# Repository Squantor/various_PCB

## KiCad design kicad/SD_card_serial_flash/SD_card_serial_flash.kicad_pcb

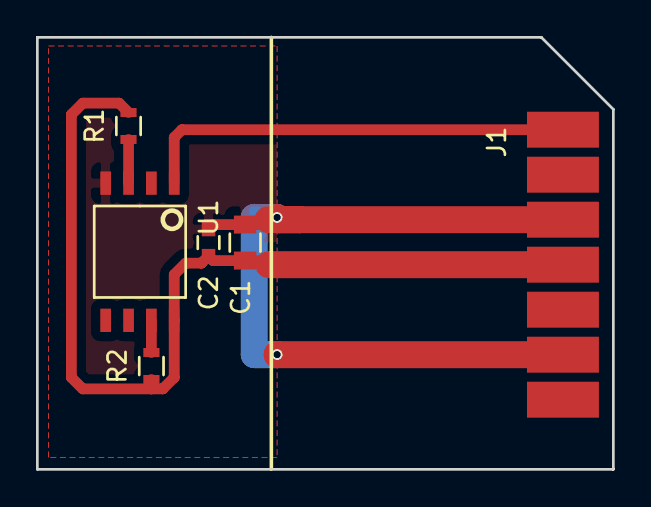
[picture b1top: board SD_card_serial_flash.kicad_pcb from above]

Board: 2 copper layers, 32.0 x 24.0 mm, 6 parts (0 on the bottom side), 8 nets.

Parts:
C1: 1u; C_0805
C2: 100n; C_0603
J1: SD_CARD_connector
R1: 10K; R_0603
R2: 10k; R_0603
U1: W25Q32BV; W25Q32BVST

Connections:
+3V3: C1.1, C2.1, J1.4, R1.2, R2.1, U1.8
CS: J1.1, U1.1
DI: J1.2, U1.5
DO: J1.7, U1.2
GND: C1.2, C2.2, J1.3, J1.6, U1.4
unnamed: R1.1, U1.3
unnamed: R2.2, U1.7
SCLK: J1.5, U1.6

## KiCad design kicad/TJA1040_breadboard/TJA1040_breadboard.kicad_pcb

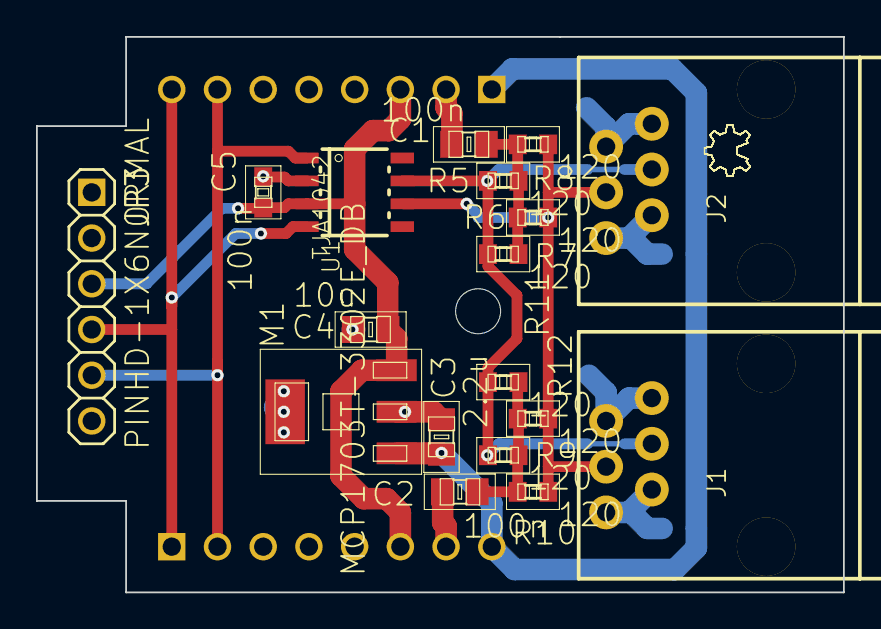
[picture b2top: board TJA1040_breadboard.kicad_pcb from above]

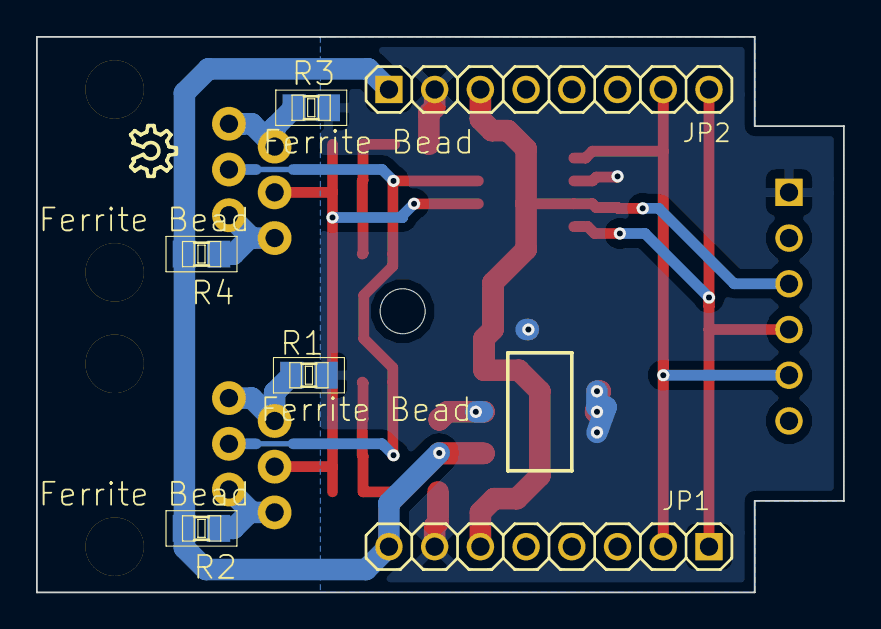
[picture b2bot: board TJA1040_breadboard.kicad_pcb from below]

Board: 2 copper layers, 44.8 x 30.9 mm, 25 parts (5 on the bottom side), 13 nets.

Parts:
C1, C2: 100n; SquantorRCL-C0805
C3: 2.2u; SquantorRCL-C0805
C4: 10u; SquantorRCL-C0805
C5: 100n; SquantorRCL-C0603
J1, J2: SquantBus_RJ11; SquantBus-RJ11
JP1, JP2: PINHD-1X8TH_NORMAL; SquantorConnectors-1X08
JP3: PINHD-1X6NORMAL; SquantorConnectors-1X06
LOGO1: OSHW_LOGO_8MILX0100-NT; ohw-logo-OSHW_8X100_NOTEXT
M1: MCP1703T-3302E_DB; SquantorMicrochip-SOT223
R1, R2, R3, R4: Ferrite Bead; SquantorRCL-R0805
R5, R6, R7, R8, R9, R10, R11, R12: 120; SquantorRCL-R0603
U1: TJA1042; SOT96-1

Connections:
+5V: C4.1, C5.2, JP1.6, JP2.3, JP3.3, M1.3, U1.3
+BATT: C3.1, JP1.8, JP2.1, M1.1, R2.2, R4.2
CAN_H: J1.4, J2.4, R5.1, R7.1, R9.1, R11.1, U1.7
CAN_L: J1.3, J2.3, R6.2, R8.2, R10.2, R12.2, U1.6
CAN_RX: JP1.1, JP2.8, JP3.4, U1.4
CAN_TX: JP1.2, JP2.7, JP3.5, U1.1
GND: C1.2, C2.1, C3.2, C4.2, C5.1, JP1.7, JP2.2, JP3.1, M1.2, M1.4, R1.2, R3.2, U1.2
unnamed: C1.1, R5.2, R6.1, R7.2, R8.1
unnamed: C2.2, R9.2, R10.1, R11.2, R12.1
unnamed: J1.1, J1.2, R2.1
unnamed: J1.5, J1.6, R1.1
unnamed: J2.1, J2.2, R4.1
unnamed: J2.5, J2.6, R3.1

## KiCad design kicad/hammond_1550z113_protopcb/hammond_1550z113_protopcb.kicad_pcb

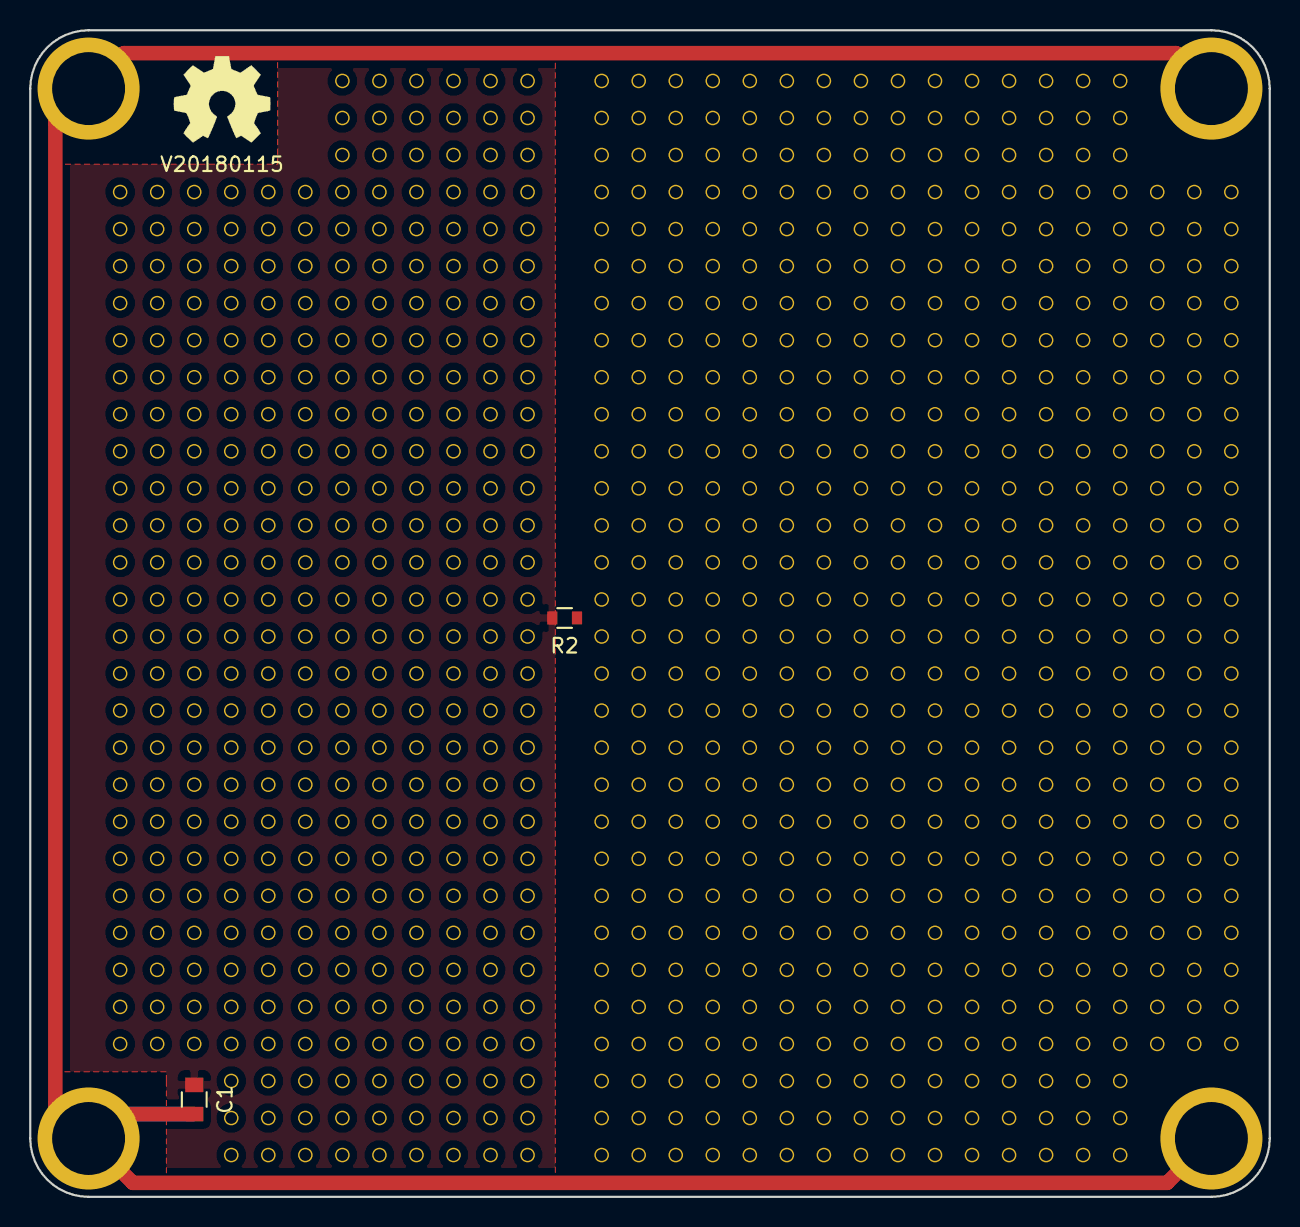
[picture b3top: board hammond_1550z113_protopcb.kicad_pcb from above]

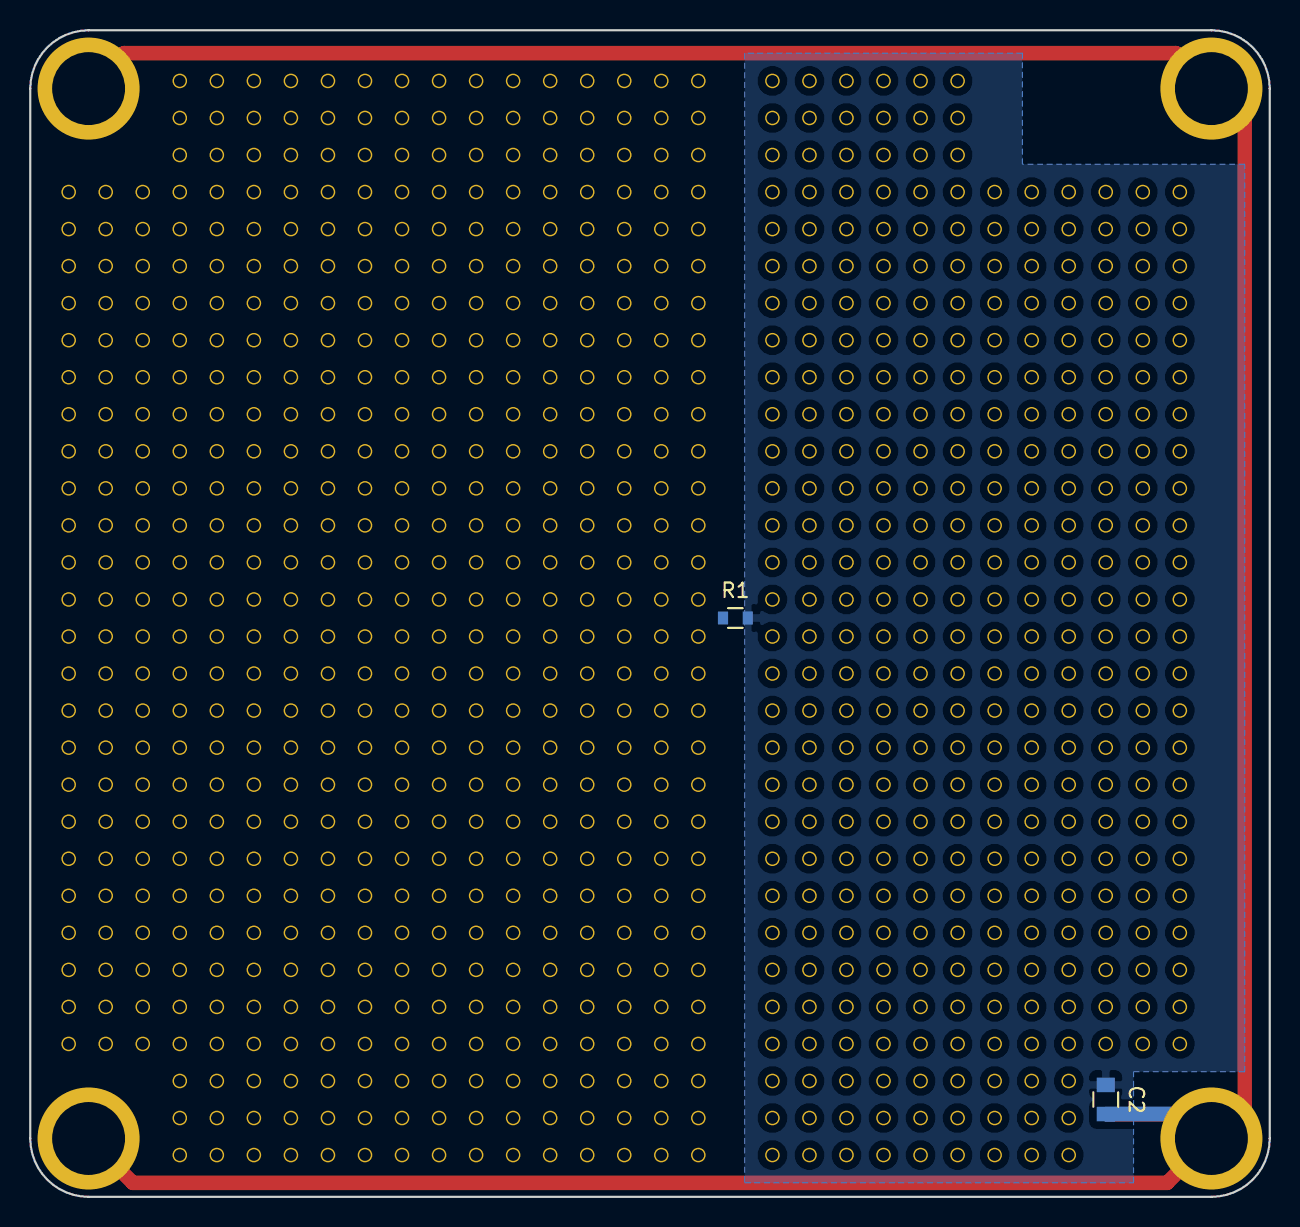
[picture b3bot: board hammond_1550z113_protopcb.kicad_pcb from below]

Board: 2 copper layers, 85.0 x 80.0 mm, 36 parts (2 on the bottom side), 3 nets.

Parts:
C1, C2: C; C_0805
H1, H2, H3, H4: Drill_Hole_connected; MountingHole_5mm_7mm_metal
J1, J2, J3, J4, J5, J6, J7, J8, J9, J10, J11, J12, J13, J14, J15, J16, J17, J18, J19, J20, J21, J22, J23: Proto; proto-TH-0254-06X06-P010SQ-H008
J24, J25, J26: Proto; proto-TH-0254-03X03-P010SQ-H008
N1: OHWLOGO; OSHW-Symbol_6.7x6mm_SilkScreen
N2: V20180115; Label_version
R1, R2: 0; R_0603_hand

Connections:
GNDREF: C1.2, C2.2, H1.S, H2.S, H3.S, H4.S
LEFT_BOT_PLANE: C2.1, R1.2
LEFT_TOP_PLANE: C1.1, R2.2

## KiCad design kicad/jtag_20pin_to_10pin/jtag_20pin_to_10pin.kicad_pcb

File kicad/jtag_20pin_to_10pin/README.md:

# 20 pin JTAG breakout to 10 pin arm style pinout
Small converter PCB that changes the 2.54mm pitch 20 pin connector to a 10 pin ARM microcontroller style pinout with a 1.27mm pitch.
## TODO's
Still some things need to be done:
* schematic entry (Done)
* PCB layout (Done)
* Review with one night in between (Done)
* Produce at [OSHPARK](https://oshpark.com/shared_projects/sNI7cM5I) (WIP)
* Assemble (TODO)
* Test & characterise (TODO)
* update Readme.md with pictures and BOM (TODO)
## BOM
TODO
## Pictures
TODO

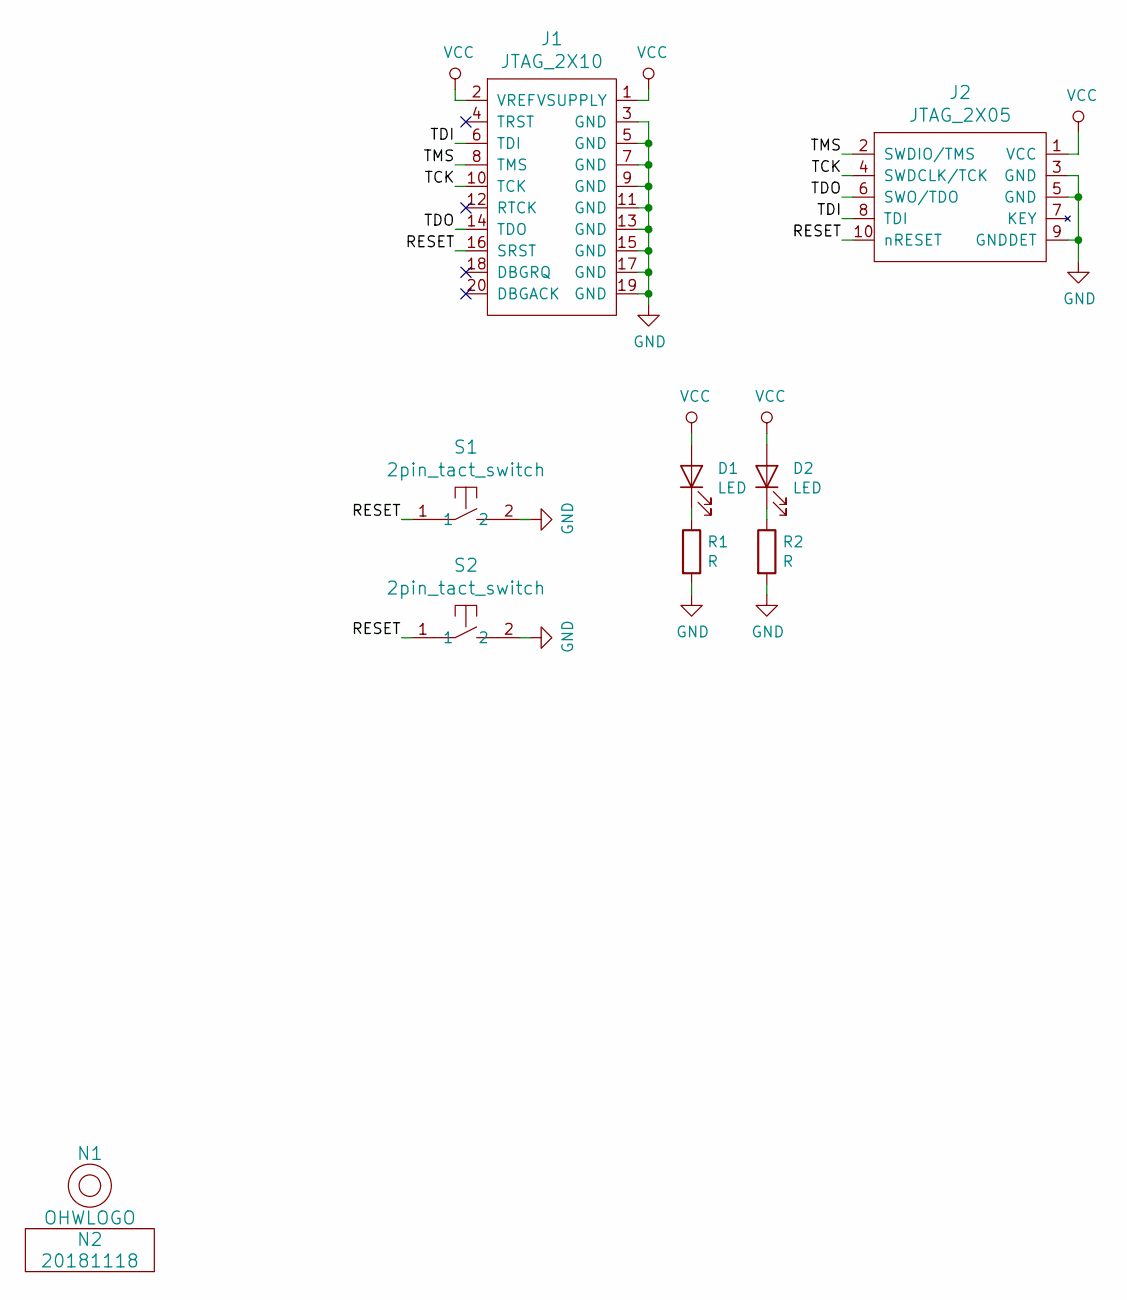
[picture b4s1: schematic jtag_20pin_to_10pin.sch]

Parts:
D1, D2: LED; R_0603_hand
J1: JTAG_2X10; Header-0245-2X10-H010
J2: JTAG_2X05; Header-Shr-0127-2X05-H006
N1: OHWLOGO; OSHW-Symbol_6.7x6mm_SilkScreen
N2: 20181118; Label_version
R1, R2: R; R_0603_hand
S1, S2: 2pin_tact_switch; TD-85XU

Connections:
/RESET: J1.16 (SRST), J2.10 (nRESET), S1.1, S2.1
/TCK: J1.10 (TCK), J2.4 (SWDCLK/TCK)
/TDI: J1.6 (TDI), J2.8 (TDI)
/TDO: J1.14 (TDO), J2.6 (SWO/TDO)
/TMS: J1.8 (TMS), J2.2 (SWDIO/TMS)
GND: J1.3 (GND), J1.5 (GND), J1.7 (GND), J1.9 (GND), J1.11 (GND), J1.13 (GND), J1.15 (GND), J1.17 (GND), J1.19 (GND), J2.3 (GND), J2.5 (GND), J2.9 (GNDDET), R1.2, R2.2, S1.2, S2.2
unnamed: D1.1 (K), R1.1
unnamed: D2.1 (K), R2.1
VCC: D1.2 (A), D2.2 (A), J1.1 (VSUPPLY), J1.2 (VREF), J2.1 (VCC)

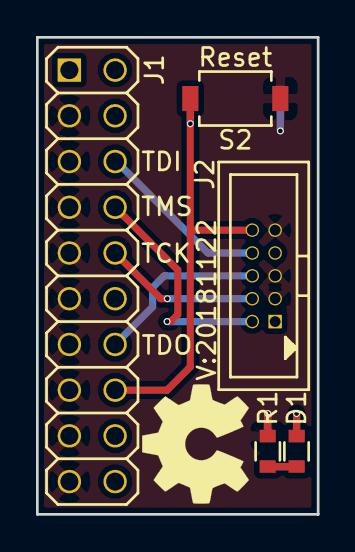
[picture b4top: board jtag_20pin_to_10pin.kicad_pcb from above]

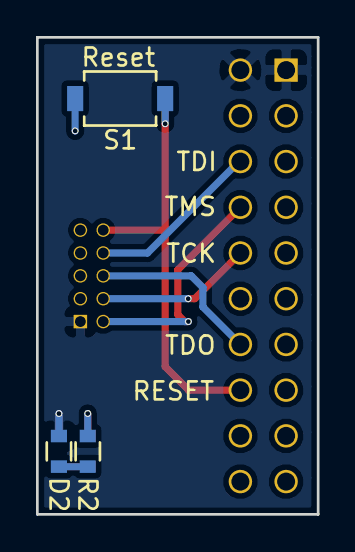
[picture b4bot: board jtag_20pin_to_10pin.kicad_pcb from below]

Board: 2 copper layers, 15.6 x 26.5 mm, 10 parts (3 on the bottom side), 9 nets.

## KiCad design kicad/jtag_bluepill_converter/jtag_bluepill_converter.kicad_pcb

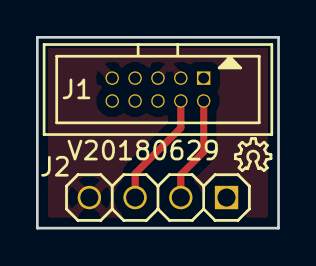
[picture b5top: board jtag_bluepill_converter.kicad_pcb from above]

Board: 2 copper layers, 13.4 x 10.6 mm, 4 parts (0 on the bottom side), 4 nets.

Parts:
J1: JTAG_2X05; Header-Shr-0127-2X05-H006
J2: Conn_01x04; Header-0254-1X04-H010
N1: OHWLOGO; ohw-logo-OSHW_6X70_NOTEXT
N2: V20180629; Label_version

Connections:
/SWDCLK: J1.4, J2.3
/SWDIO: J1.2, J2.2
VDD: J1.1, J2.1
VSS: J1.3, J1.5, J1.9, J2.4
